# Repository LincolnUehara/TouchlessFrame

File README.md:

# Touchless Frame
Customizable frame made of infrared sensors to promote contactless interface

This repository contains Kicad and Freecad related files to Touchless Frame Project.

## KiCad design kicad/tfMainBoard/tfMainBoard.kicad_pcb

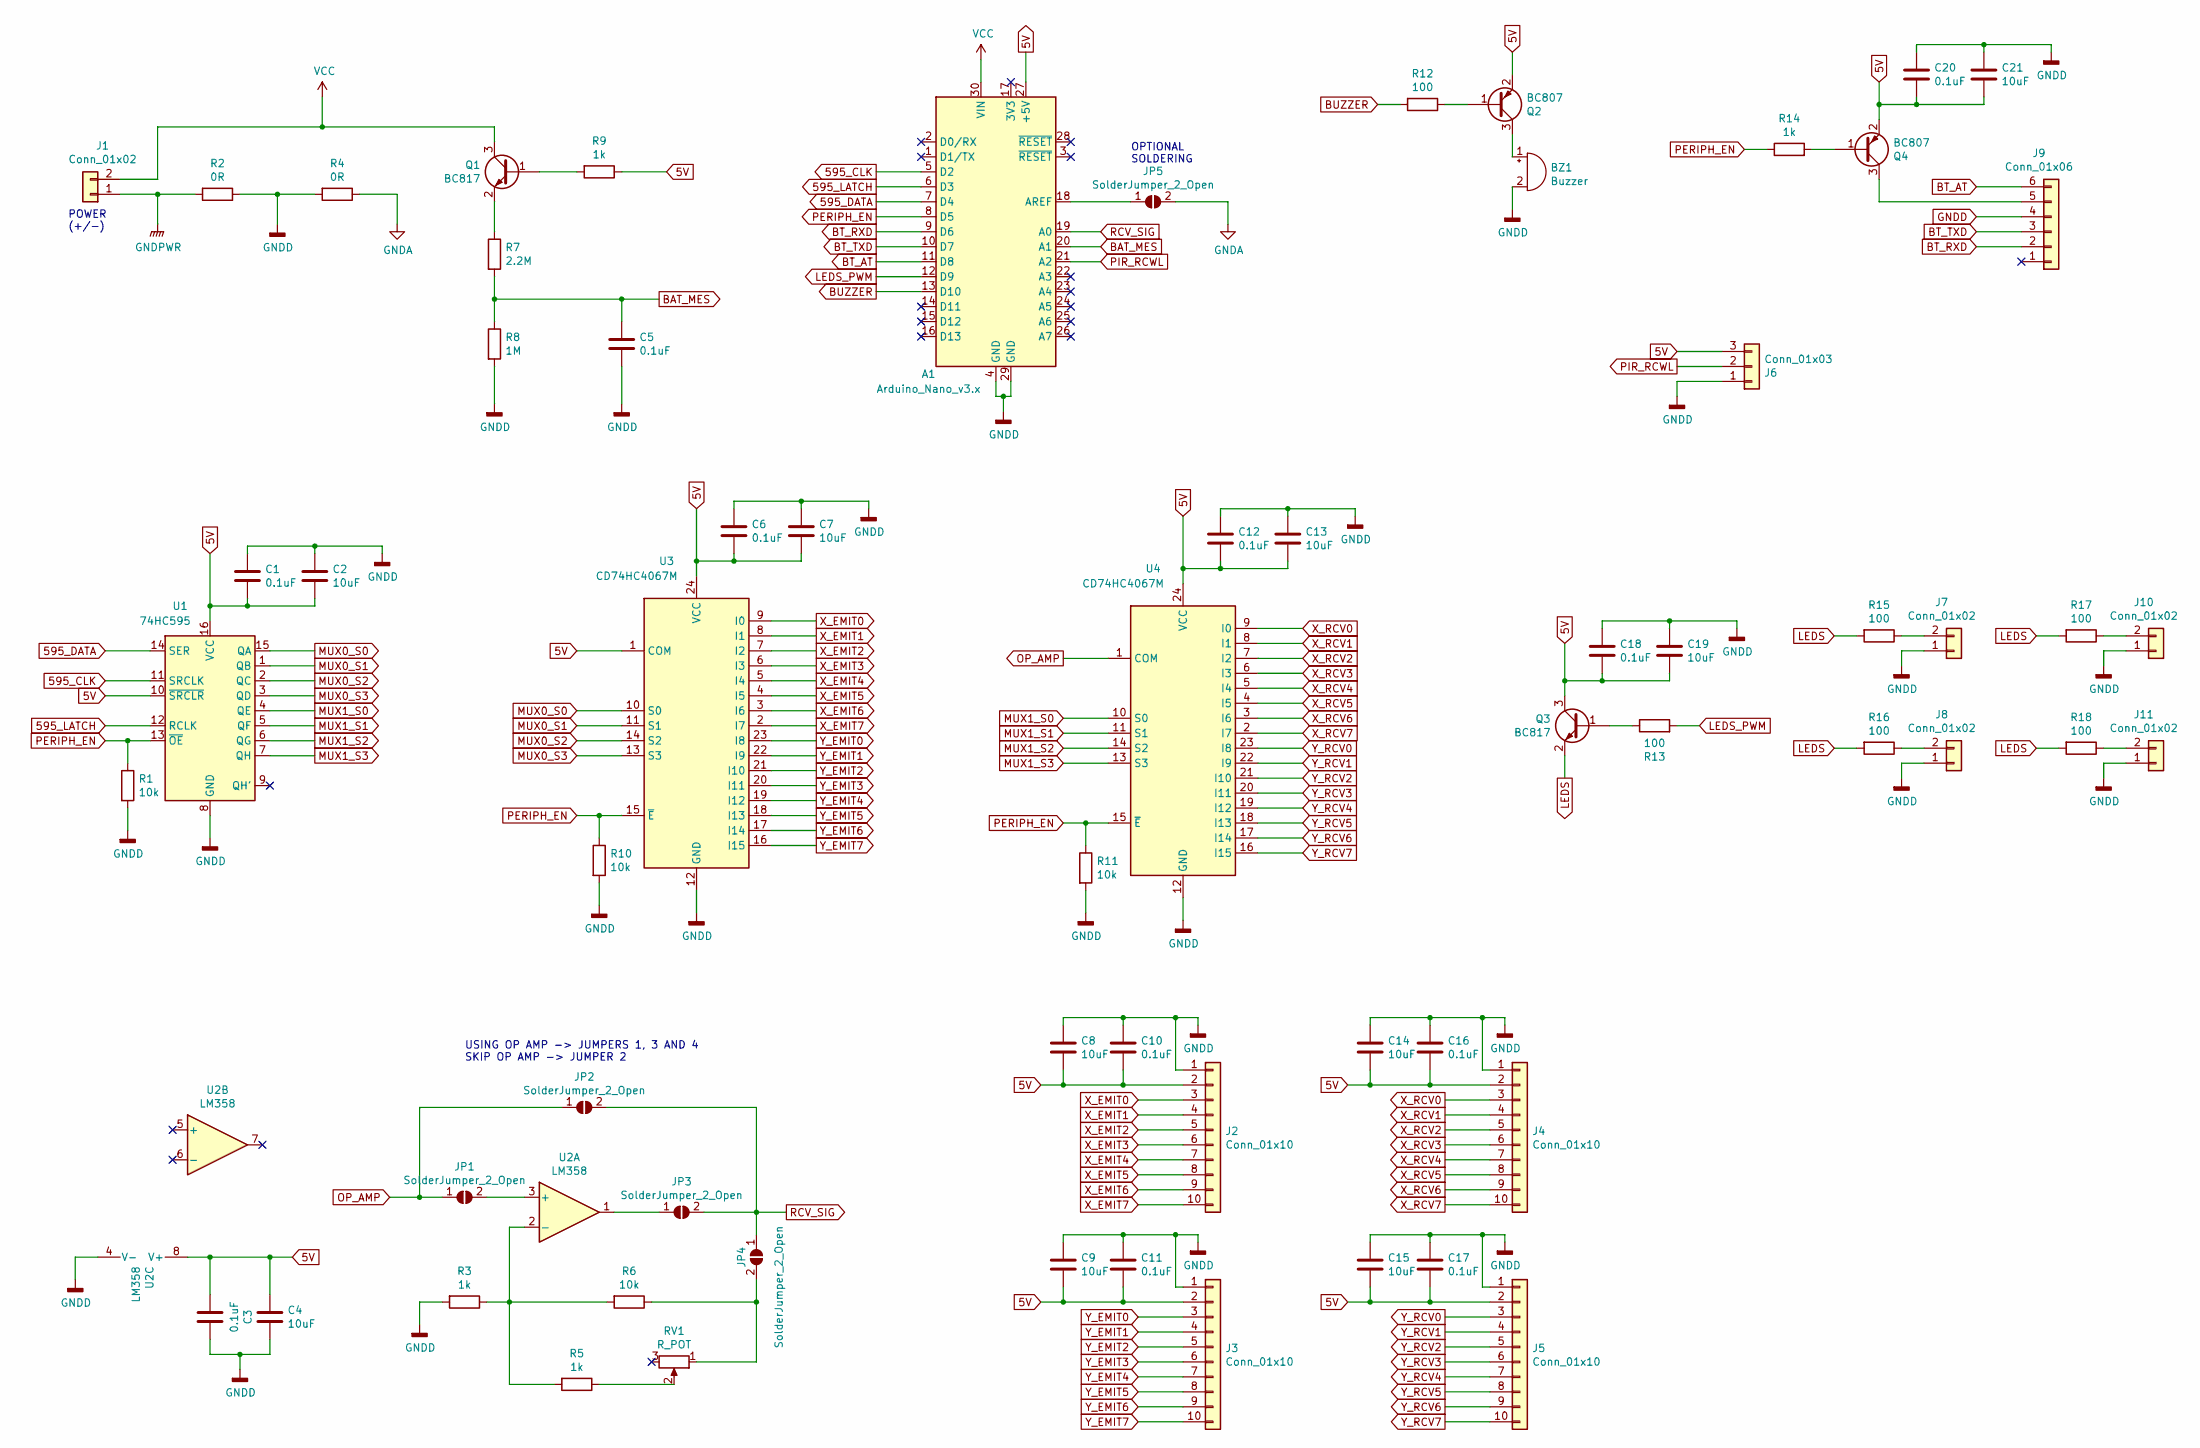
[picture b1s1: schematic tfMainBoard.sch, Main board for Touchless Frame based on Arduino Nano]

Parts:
A1: Arduino_Nano_v3.x; Arduino_Nano
BZ1: Buzzer; Buzzer_12x9.5RM7.6
C1, C3, C5, C6, C10, C11, C12, C16, C17, C18, C20: 0.1uF; C_0603_1608Metric
C2, C4, C7, C8, C9, C13, C14, C15, C19, C21: 10uF; C_0603_1608Metric
J1, J7, J8, J10, J11: Conn_01x02; PinHeader_1x02_P2.54mm_Vertical
J2, J3, J4, J5: Conn_01x10; PinHeader_1x10_P2.54mm_Vertical
J6: Conn_01x03; PinHeader_1x03_P2.54mm_Vertical
J9: Conn_01x06; PinHeader_1x06_P2.54mm_Vertical
JP1, JP2, JP3, JP4, JP5: SolderJumper_2_Open; SolderJumper-2_P1.3mm_Open_RoundedPad1.0x1.5mm
Q1, Q3: BC817; SOT-23
Q2, Q4: BC807; SOT-23
R1, R6, R10, R11: 10k; R_0603_1608Metric
R2, R4: 0R; R_1210_3225Metric
R3, R5, R9, R14: 1k; R_0603_1608Metric
R7: 2.2M; R_0603_1608Metric
R8: 1M; R_0603_1608Metric
R12, R13, R15, R16, R17, R18: 100; R_0603_1608Metric
RV1: R_POT; Potentiometer_Bourns_3214X_Vertical
U1: 74HC595; SOIC-16_3.9x9.9mm_P1.27mm
U2: LM358; SOIC-8_3.9x4.9mm_P1.27mm
U3, U4: CD74HC4067M; SSOP-24_5.3x8.2mm_P0.65mm

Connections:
5V: A1.27 (+5V), C1.2, C2.2, C3.2, C4.1, C6.2, C7.2, C8.2, C9.2, C10.2, C11.2, C12.2, C13.2, C14.2, C15.2, C16.2, C17.2, C18.2, C19.2, C20.2, C21.2, J2.2, J3.2, J4.2, J5.2, J6.3, Q2.2 (E), Q3.3 (C), Q4.2 (E), R9.1, U1.10 (~SRCLR), U1.16 (VCC), U2.8 (V+), U3.1 (COM), U3.24 (VCC), U4.24 (VCC)
595_CLK: A1.5 (D2), U1.11 (SRCLK)
595_DATA: A1.7 (D4), U1.14 (SER)
595_LATCH: A1.6 (D3), U1.12 (RCLK)
BAT_MES: A1.20 (A1), C5.1, R7.2, R8.1
BT_AT: A1.11 (D8), J9.6
BT_RXD: A1.9 (D6), J9.2
BT_TXD: A1.10 (D7), J9.3
BUZZER: A1.13 (D10), R12.2
GNDA: JP5.2 (B), R4.1
GNDD: A1.4 (GND), A1.29 (GND), BZ1.2 (+), C1.1, C2.1, C3.1, C4.2, C5.2, C6.1, C7.1, C8.1, C9.1, C10.1, C11.1, C12.1, C13.1, C14.1, C15.1, C16.1, C17.1, C18.1, C19.1, C20.1, C21.1, J2.1, J3.1, J4.1, J5.1, J6.1, J7.1, J8.1, J9.4, J10.1, J11.1, R1.2, R2.1, R3.2, R4.2, R8.2, R10.2, R11.2, U1.8 (GND), U2.4 (V-), U3.12 (GND), U4.12 (GND)
GNDPWR: J1.1, R2.2
LEDS: Q3.2 (E), R15.2, R16.2, R17.2, R18.2
LEDS_PWM: A1.12 (D9), R13.2
MUX0_S0: U1.15 (QA), U3.10 (S0)
MUX0_S1: U1.1 (QB), U3.11 (S1)
MUX0_S2: U1.2 (QC), U3.14 (S2)
MUX0_S3: U1.3 (QD), U3.13 (S3)
MUX1_S0: U1.4 (QE), U4.10 (S0)
MUX1_S1: U1.5 (QF), U4.11 (S1)
MUX1_S2: U1.6 (QG), U4.14 (S2)
MUX1_S3: U1.7 (QH), U4.13 (S3)
unnamed: A1.18 (AREF), JP5.1 (A)
unnamed: BZ1.1 (-), Q2.3 (C)
unnamed: J7.2, R15.1
unnamed: J8.2, R16.1
unnamed: J9.5, Q4.3 (C)
unnamed: J10.2, R17.1
unnamed: J11.2, R18.1
unnamed: JP1.2 (B), U2.3 (+)
unnamed: JP3.1 (A), U2.1
unnamed: JP4.2 (B), R6.1, RV1.1
unnamed: Q1.1 (B), R9.2
unnamed: Q1.2 (E), R7.1
unnamed: Q2.1 (B), R12.1
unnamed: Q3.1 (B), R13.1
unnamed: Q4.1 (B), R14.2
unnamed: R3.1, R5.2, R6.2, U2.2 (-)
unnamed: R5.1, RV1.2
OP_AMP: JP1.1 (A), JP2.1 (A), U4.1 (COM)
PERIPH_EN: A1.8 (D5), R1.1, R10.1, R11.1, R14.1, U1.13 (~OE), U3.15 (~E), U4.15 (~E)
PIR_RCWL: A1.21 (A2), J6.2
RCV_SIG: A1.19 (A0), JP2.2 (B), JP3.2 (B), JP4.1 (A)
VCC: A1.30 (VIN), J1.2, Q1.3 (C)
X_EMIT0: J2.3, U3.9 (I0)
X_EMIT1: J2.4, U3.8 (I1)
X_EMIT2: J2.5, U3.7 (I2)
X_EMIT3: J2.6, U3.6 (I3)
X_EMIT4: J2.7, U3.5 (I4)
X_EMIT5: J2.8, U3.4 (I5)
X_EMIT6: J2.9, U3.3 (I6)
X_EMIT7: J2.10, U3.2 (I7)
X_RCV0: J4.3, U4.9 (I0)
X_RCV1: J4.4, U4.8 (I1)
X_RCV2: J4.5, U4.7 (I2)
X_RCV3: J4.6, U4.6 (I3)
X_RCV4: J4.7, U4.5 (I4)
X_RCV5: J4.8, U4.4 (I5)
X_RCV6: J4.9, U4.3 (I6)
X_RCV7: J4.10, U4.2 (I7)
Y_EMIT0: J3.3, U3.23 (I8)
Y_EMIT1: J3.4, U3.22 (I9)
Y_EMIT2: J3.5, U3.21 (I10)
Y_EMIT3: J3.6, U3.20 (I11)
Y_EMIT4: J3.7, U3.19 (I12)
Y_EMIT5: J3.8, U3.18 (I13)
Y_EMIT6: J3.9, U3.17 (I14)
Y_EMIT7: J3.10, U3.16 (I15)
Y_RCV0: J5.3, U4.23 (I8)
Y_RCV1: J5.4, U4.22 (I9)
Y_RCV2: J5.5, U4.21 (I10)
Y_RCV3: J5.6, U4.20 (I11)
Y_RCV4: J5.7, U4.19 (I12)
Y_RCV5: J5.8, U4.18 (I13)
Y_RCV6: J5.9, U4.17 (I14)
Y_RCV7: J5.10, U4.16 (I15)

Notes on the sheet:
POWER (+/-)
OPTIONAL SOLDERING
USING OP AMP -> JUMPERS 1, 3 AND 4 SKIP OP AMP -> JUMPER 2

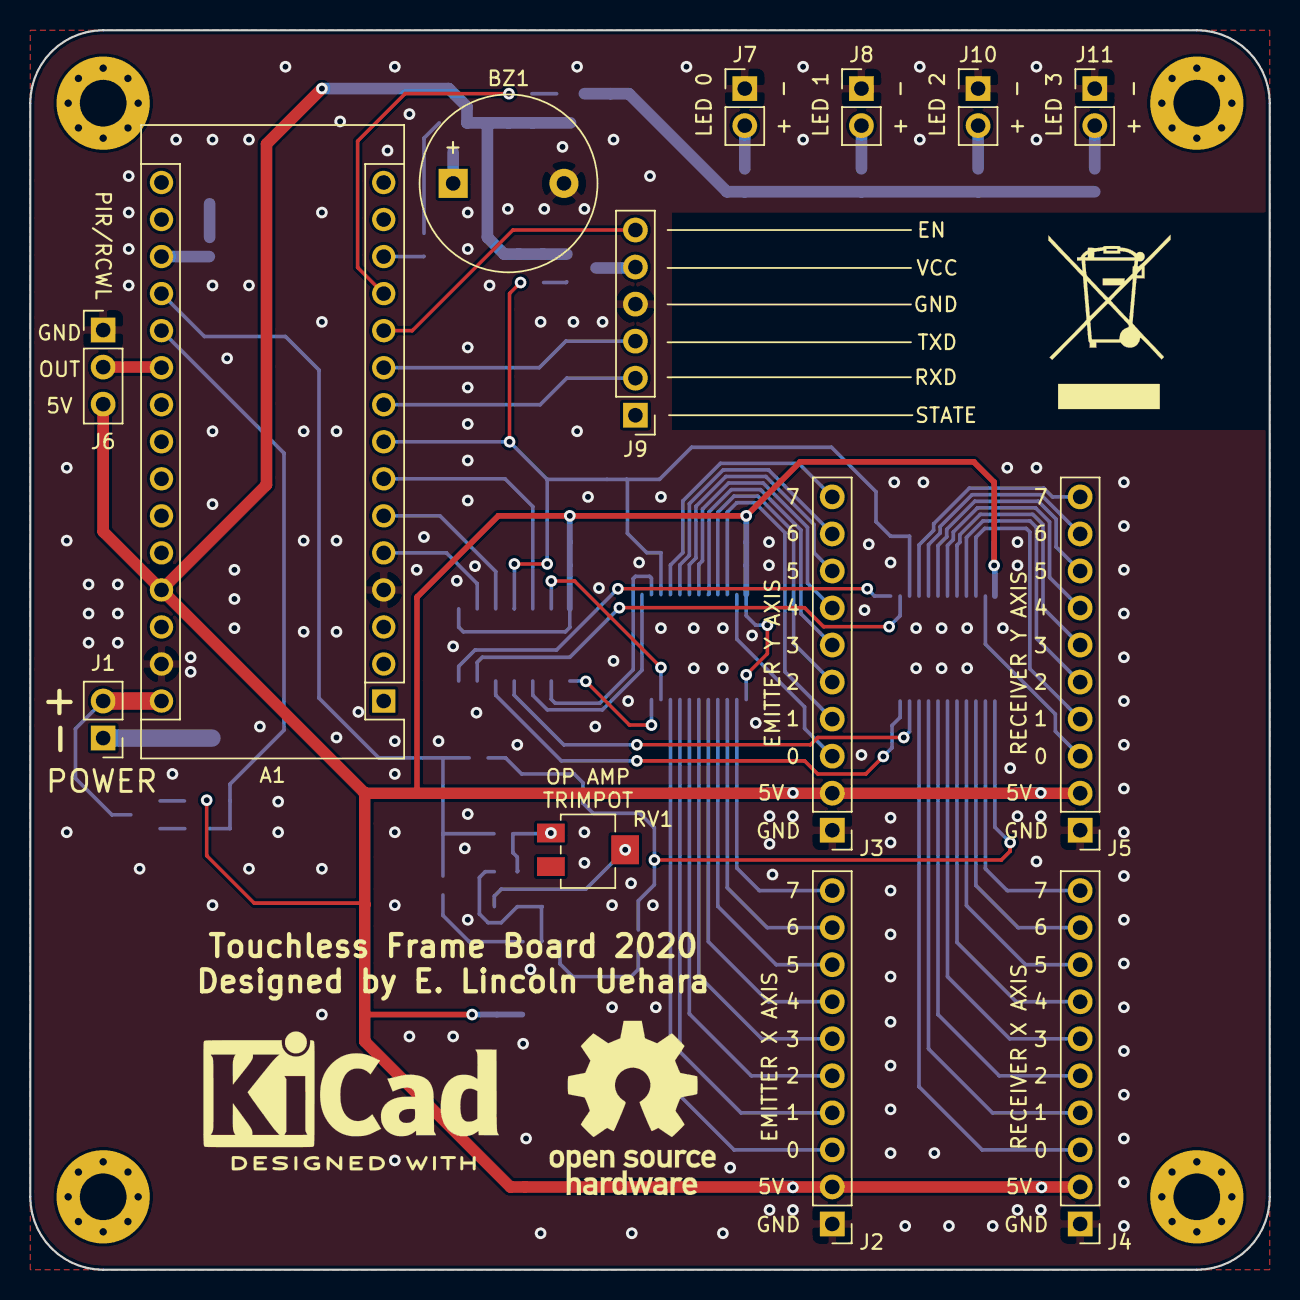
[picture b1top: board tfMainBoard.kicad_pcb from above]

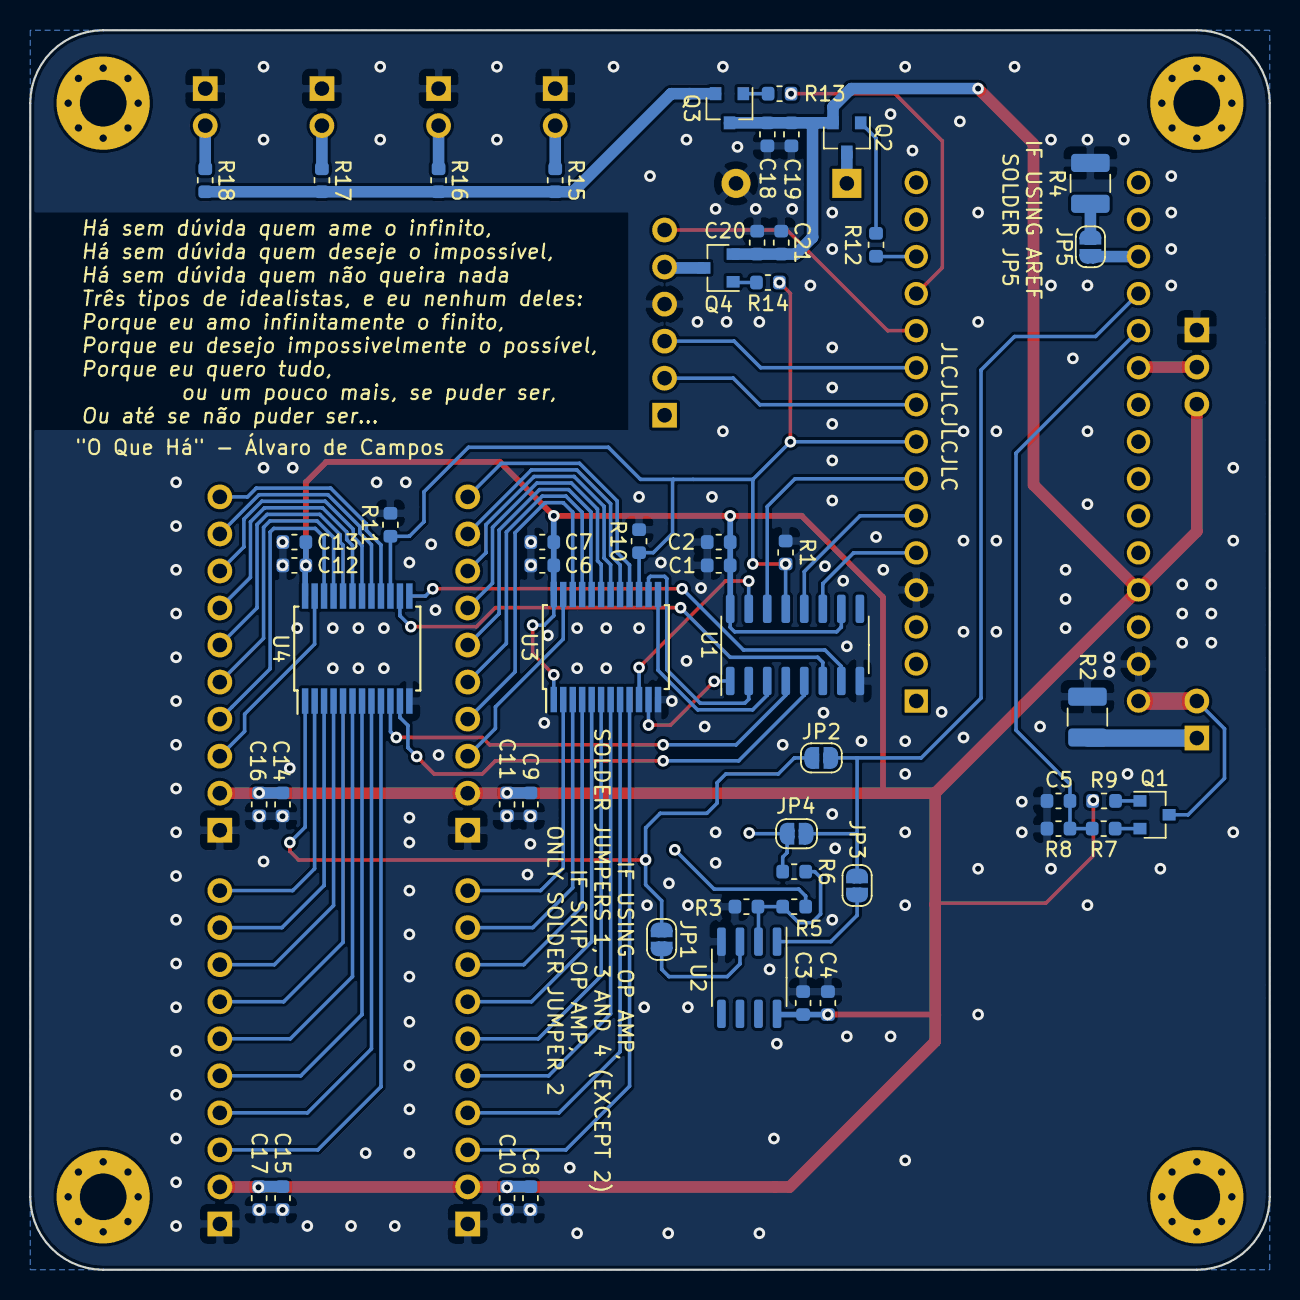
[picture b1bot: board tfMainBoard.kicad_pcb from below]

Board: 2 copper layers, 85.0 x 85.0 mm, 66 parts (52 on the bottom side), 76 nets.

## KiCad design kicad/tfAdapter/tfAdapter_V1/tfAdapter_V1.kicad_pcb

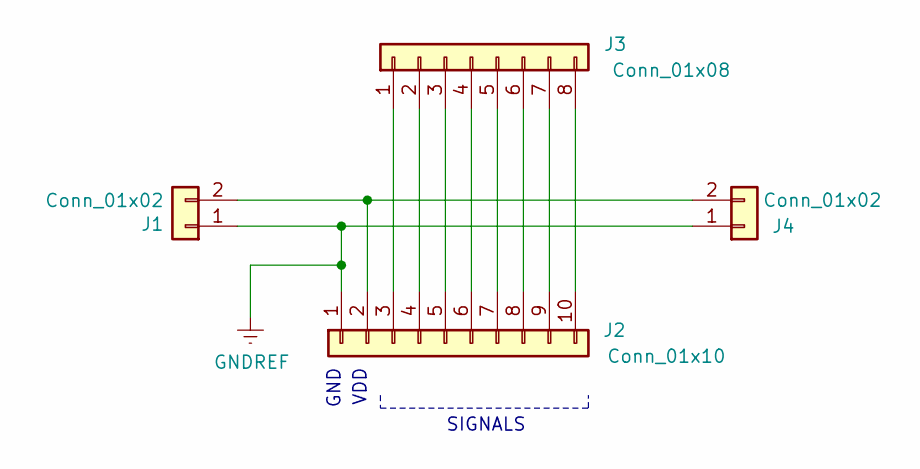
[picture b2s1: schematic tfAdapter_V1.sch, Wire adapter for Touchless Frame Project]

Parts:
J1, J4: Conn_01x02; PinHeader_1x02_P2.54mm_Vertical
J2: Conn_01x10; PinHeader_1x10_P2.54mm_Vertical
J3: Conn_01x08; PinHeader_1x08_P2.54mm_Vertical

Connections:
GNDREF: J1.1, J2.1, J4.1
unnamed: J1.2, J2.2, J4.2
unnamed: J2.3, J3.1
unnamed: J2.4, J3.2
unnamed: J2.5, J3.3
unnamed: J2.6, J3.4
unnamed: J2.7, J3.5
unnamed: J2.8, J3.6
unnamed: J2.9, J3.7
unnamed: J2.10, J3.8

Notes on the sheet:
VDD
GND
SIGNALS

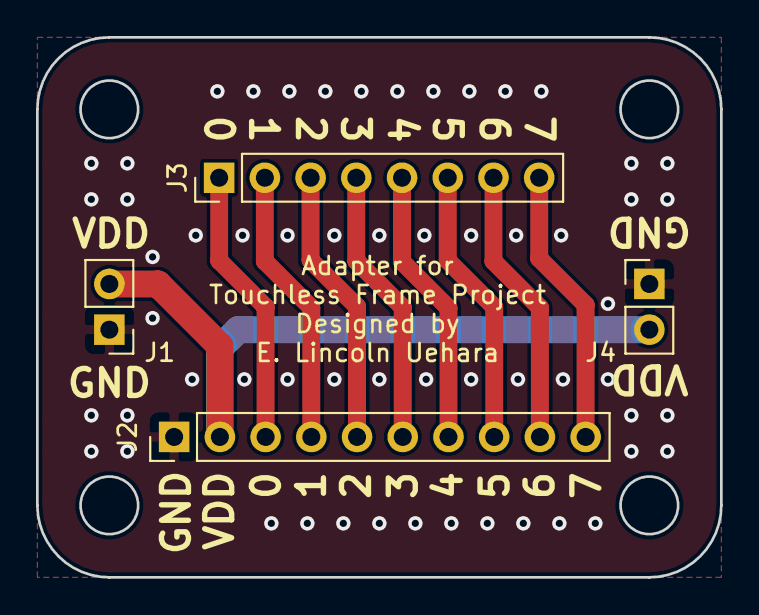
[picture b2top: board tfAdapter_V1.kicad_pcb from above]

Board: 2 copper layers, 38.0 x 30.0 mm, 4 parts (0 on the bottom side), 10 nets.

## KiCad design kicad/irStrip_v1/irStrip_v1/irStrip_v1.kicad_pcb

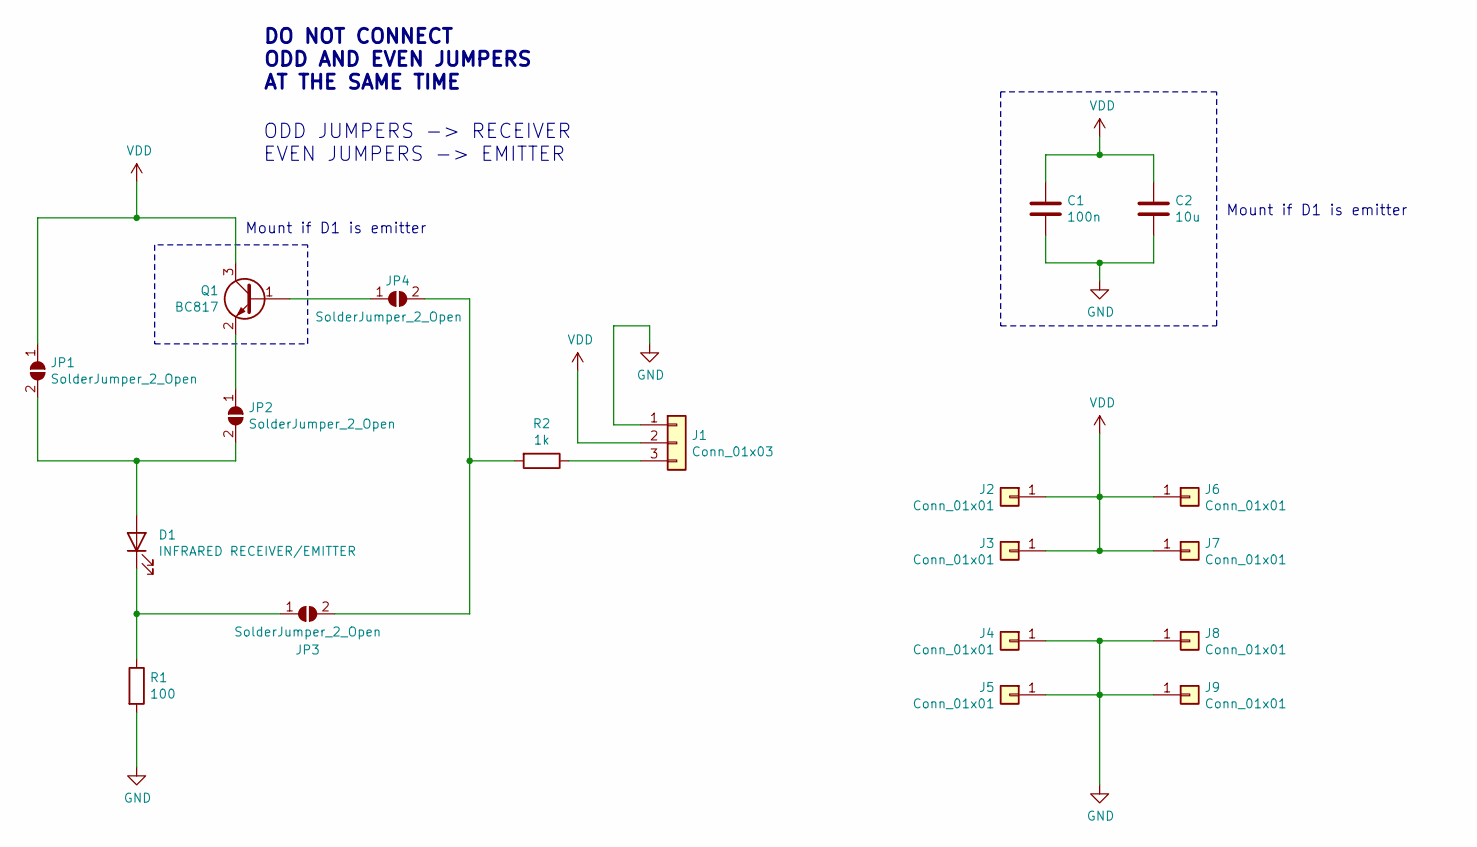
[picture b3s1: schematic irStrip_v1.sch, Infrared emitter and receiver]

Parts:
C1: 100n; C_0603_1608Metric
C2: 10u; C_0603_1608Metric
D1: INFRARED RECEIVER/EMITTER; LED_D5.0mm
J1: Conn_01x03; PinHeader_1x03_P2.54mm_Vertical
J2, J3, J4, J5, J6, J7, J8, J9: Conn_01x01; TestPoint_Pad_2.0x2.0mm
JP1, JP2, JP3, JP4: SolderJumper_2_Open; SolderJumper-2_P1.3mm_Open_RoundedPad1.0x1.5mm
Q1: BC817; SOT-23
R1: 100; R_0603_1608Metric
R2: 1k; R_0603_1608Metric

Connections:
GND: C1.2, C2.2, J1.1, J4.1, J5.1, J8.1, J9.1, R1.2
unnamed: D1.1 (K), JP3.1 (A), R1.1
unnamed: D1.2 (A), JP1.2 (B), JP2.2 (B)
unnamed: J1.3, R2.1
unnamed: JP2.1 (A), Q1.2 (E)
unnamed: JP3.2 (B), JP4.2 (B), R2.2
unnamed: JP4.1 (A), Q1.1 (B)
VDD: C1.1, C2.1, J1.2, J2.1, J3.1, J6.1, J7.1, JP1.1 (A), Q1.3 (C)

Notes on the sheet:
DO NOT CONNECT ODD AND EVEN JUMPERS AT THE SAME TIME
ODD JUMPERS -> RECEIVER EVEN JUMPERS -> EMITTER
Mount if D1 is emitter

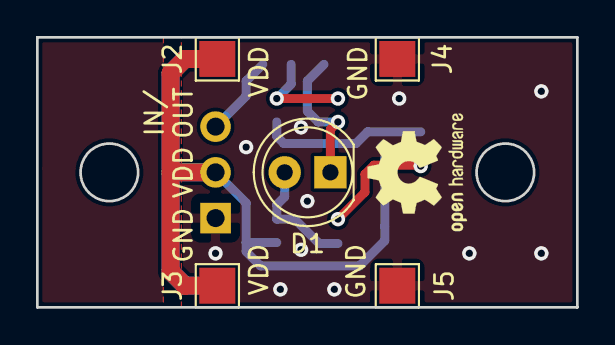
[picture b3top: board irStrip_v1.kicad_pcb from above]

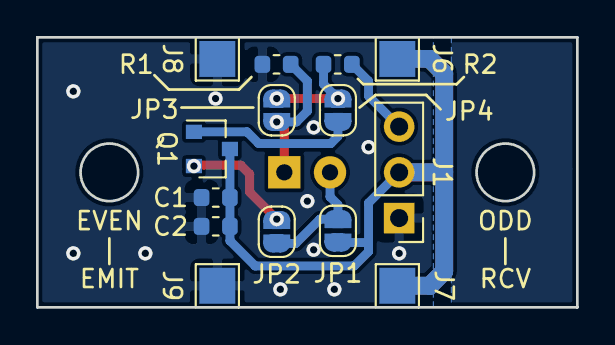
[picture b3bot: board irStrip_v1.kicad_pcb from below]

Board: 2 copper layers, 30.0 x 15.0 mm, 19 parts (14 on the bottom side), 8 nets.

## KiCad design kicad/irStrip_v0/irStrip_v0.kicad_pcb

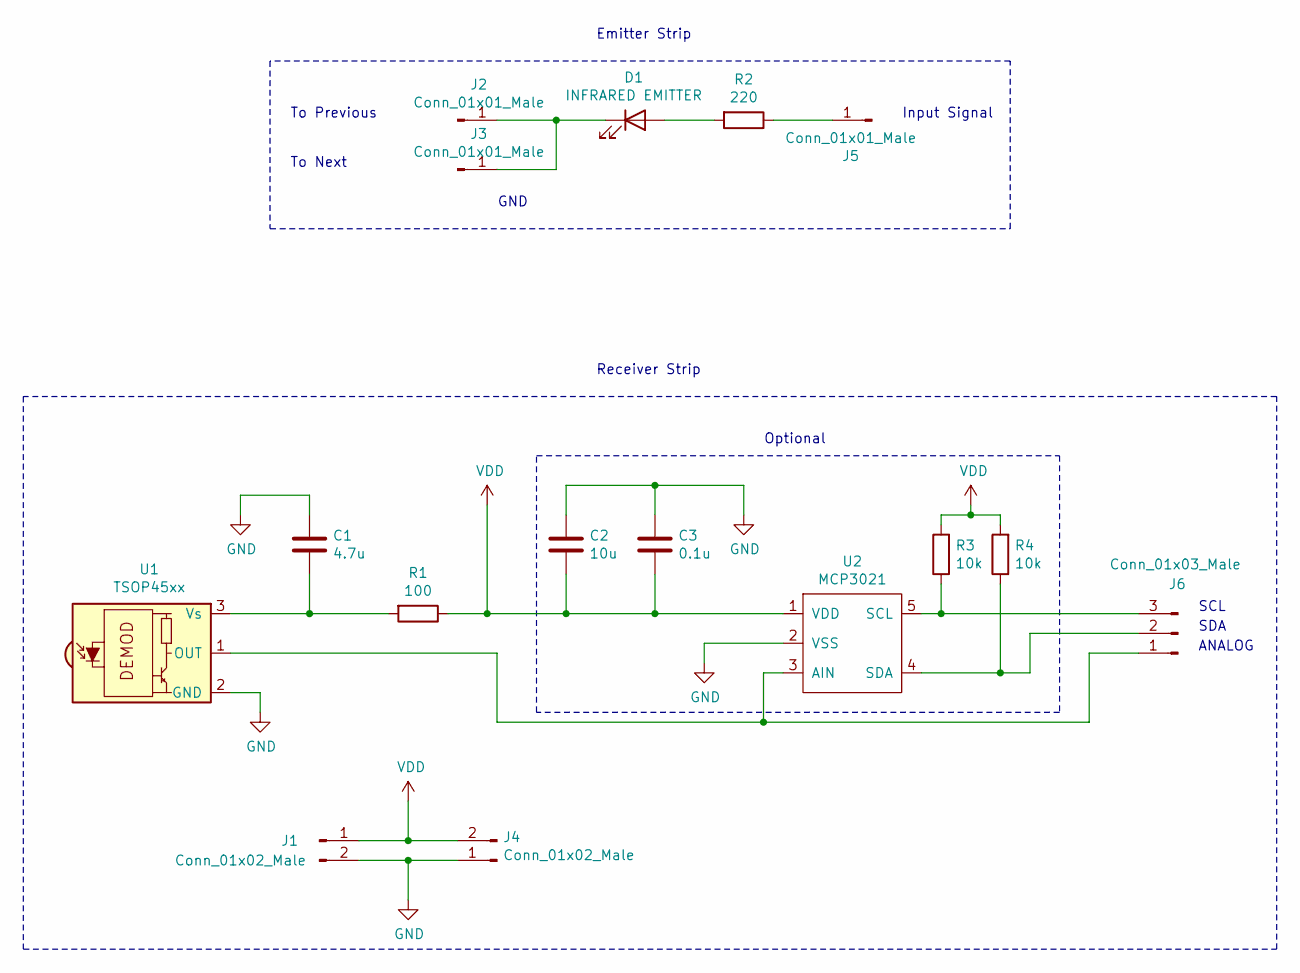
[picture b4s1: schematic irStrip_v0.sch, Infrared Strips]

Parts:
C1: 4.7u; C_0603_1608Metric
C2: 10u; C_0603_1608Metric
C3: 0.1u; C_0603_1608Metric
D1: INFRARED EMITTER; LED_D5.0mm
J1, J4: Conn_01x02_Male; PinHeader_1x02_P2.54mm_Vertical
J2, J3, J5: Conn_01x01_Male; PinHeader_1x01_P2.54mm_Vertical
J6: Conn_01x03_Male; PinHeader_1x03_P2.54mm_Vertical
R1: 100; R_0603_1608Metric
R2: 220; R_0603_1608Metric
R3, R4: 10k; R_0603_1608Metric
U1: TSOP45xx; infrared_lie_down
U2: MCP3021; SOT-23-5

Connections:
GND: C1.1, C2.1, C3.1, J1.2, J4.1, U1.2 (GND), U2.2 (VSS)
unnamed: C1.2, R1.2, U1.3 (Vs)
unnamed: D1.1 (K), J2.1, J3.1
unnamed: D1.2 (A), R2.2
unnamed: J5.1, R2.1
unnamed: J6.1, U1.1 (OUT), U2.3 (AIN)
unnamed: J6.2, R4.1, U2.4 (SDA)
unnamed: J6.3, R3.1, U2.5 (SCL)
VDD: C2.2, C3.2, J1.1, J4.2, R1.1, R3.2, R4.2, U2.1 (VDD)

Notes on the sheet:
Optional
To Previous
To Next
Input Signal
Emitter Strip
Receiver Strip
GND
SCL
SDA
ANALOG

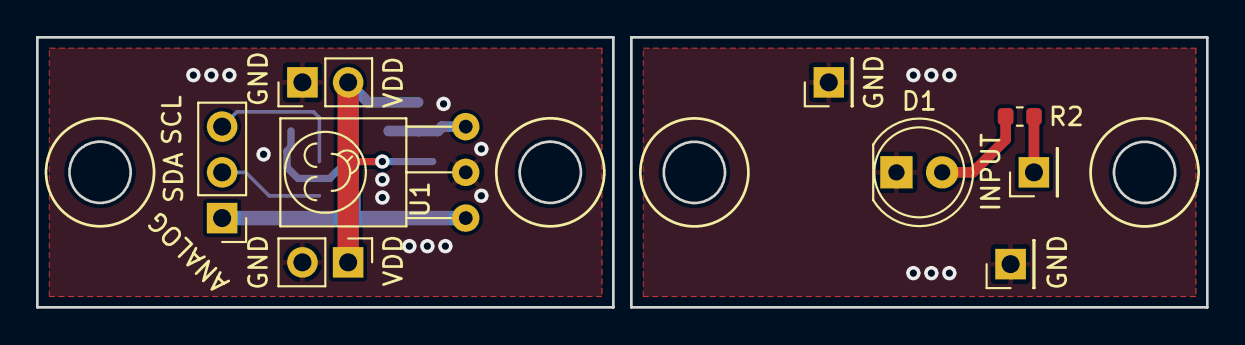
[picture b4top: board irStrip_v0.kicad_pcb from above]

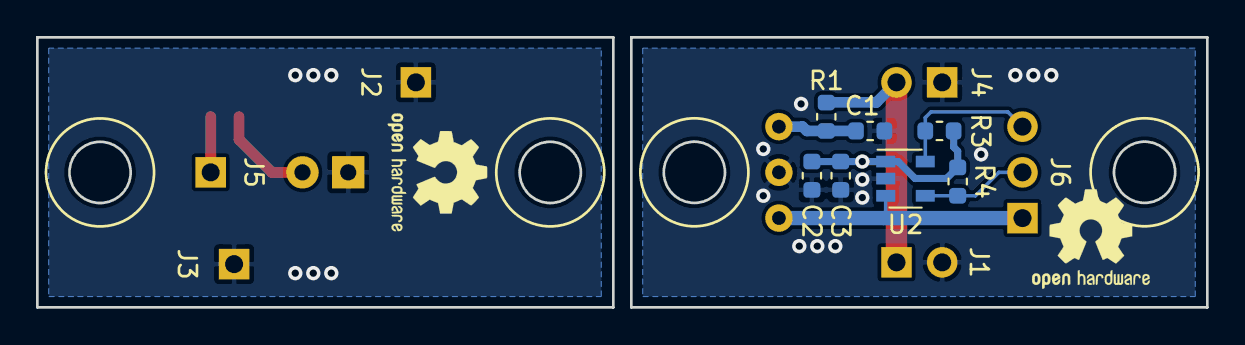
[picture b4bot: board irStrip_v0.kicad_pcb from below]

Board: 2 copper layers, 65.0 x 15.0 mm, 16 parts (7 on the bottom side), 9 nets.

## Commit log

2020-08-31 Pushing the project
